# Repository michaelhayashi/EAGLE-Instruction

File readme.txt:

Dimensions: 1.500 in. wide x 1.450 in. tall
Area: 2.175 in.^2
Copies: 1 (one)

Contact:
Michael Hayashi
Purdue IEEE Student Organization
Email: mhayashi@purdue.edu
Phone: (309) 370-4274

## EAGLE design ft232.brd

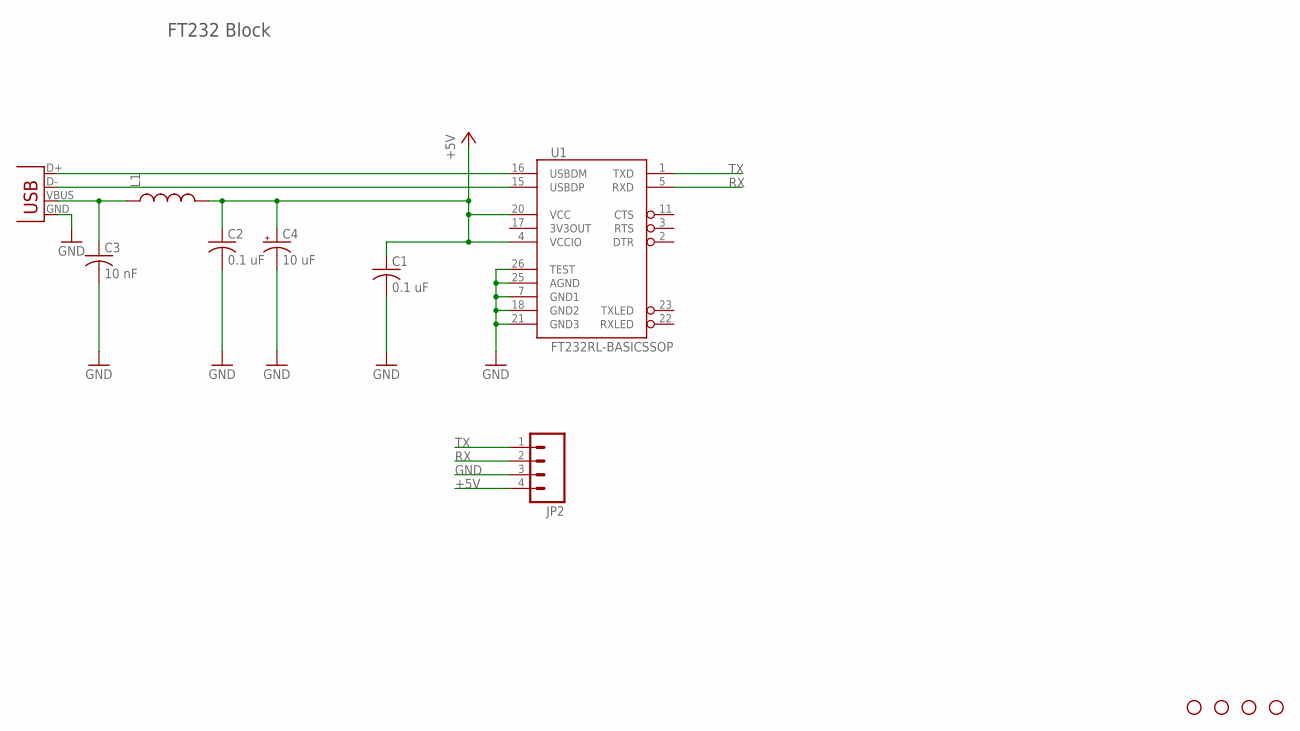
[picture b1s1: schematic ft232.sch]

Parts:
C1, C2: 0.1 uF; C0603
C3: 10 nF; C0603
C4: 10 uF; EIA3216
JP1: USB-B; USB-B-PTH
JP2: M04PTH; 1X04
L1: INDUCTOR0603; 0603
STANDOFF1, STANDOFF2, STANDOFF3, STANDOFF4: STAND-OFF
U1: FT232RL-BASICSSOP; SSOP28DB

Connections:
+5V: C1.1, C2.1, C4.A (+), JP2.4, L1.2, U1.4 (VCCIO), U1.20 (VCC)
GND: C1.2, C2.2, C3.2, C4.C (-), JP1.GND, JP2.3, U1.7 (GND1), U1.18 (GND2), U1.21 (GND3), U1.25 (AGND), U1.26 (TEST)
unnamed: C3.1, JP1.VBUS, L1.1
unnamed: JP1.D+, U1.16 (USBDM)
unnamed: JP1.D-, U1.15 (USBDP)
RX: JP2.2, U1.5 (RXD)
TX: JP2.1, U1.1 (TXD)

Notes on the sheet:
FT232 Block

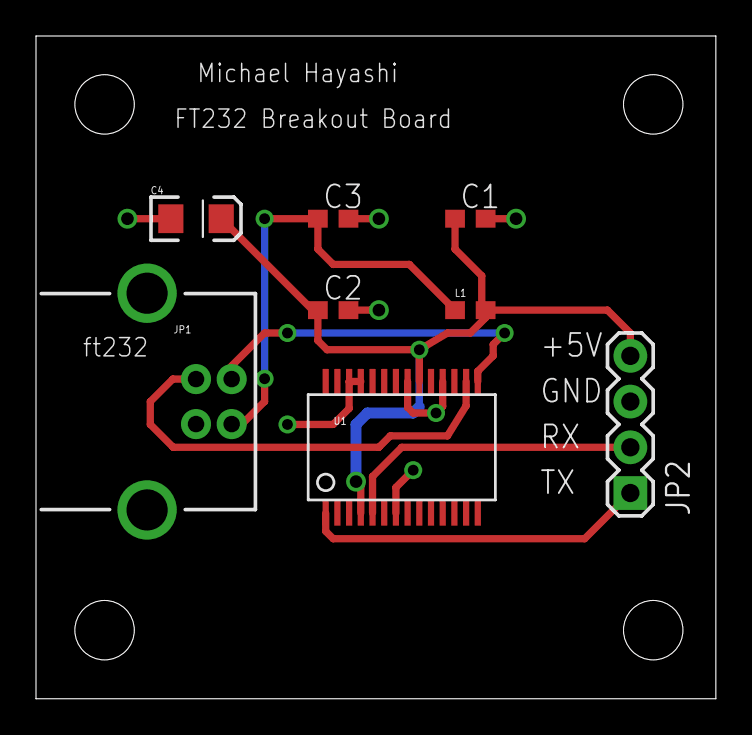
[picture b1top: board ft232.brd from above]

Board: 2 copper layers, 37.8 x 36.8 mm, 12 parts (0 on the bottom side), 7 nets.

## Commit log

2015-09-30 :tada: Added .gitattributes & .gitignore files
2015-09-30 Added Schematic and Board from Instruction #1
    Relevant EAGLE files added
2015-10-01 Added CAM files
2015-10-07 Archive of Gerbers Added
    Zipped up the gerbers with a readme
2015-10-08 Library Tutorial File Added

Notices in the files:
parts and their libraries:
SparkFun-Capacitors: Licensing: Creative Commons ShareAlike 4.0 International - https://creativecommons.org/licenses/by-sa/4.0
